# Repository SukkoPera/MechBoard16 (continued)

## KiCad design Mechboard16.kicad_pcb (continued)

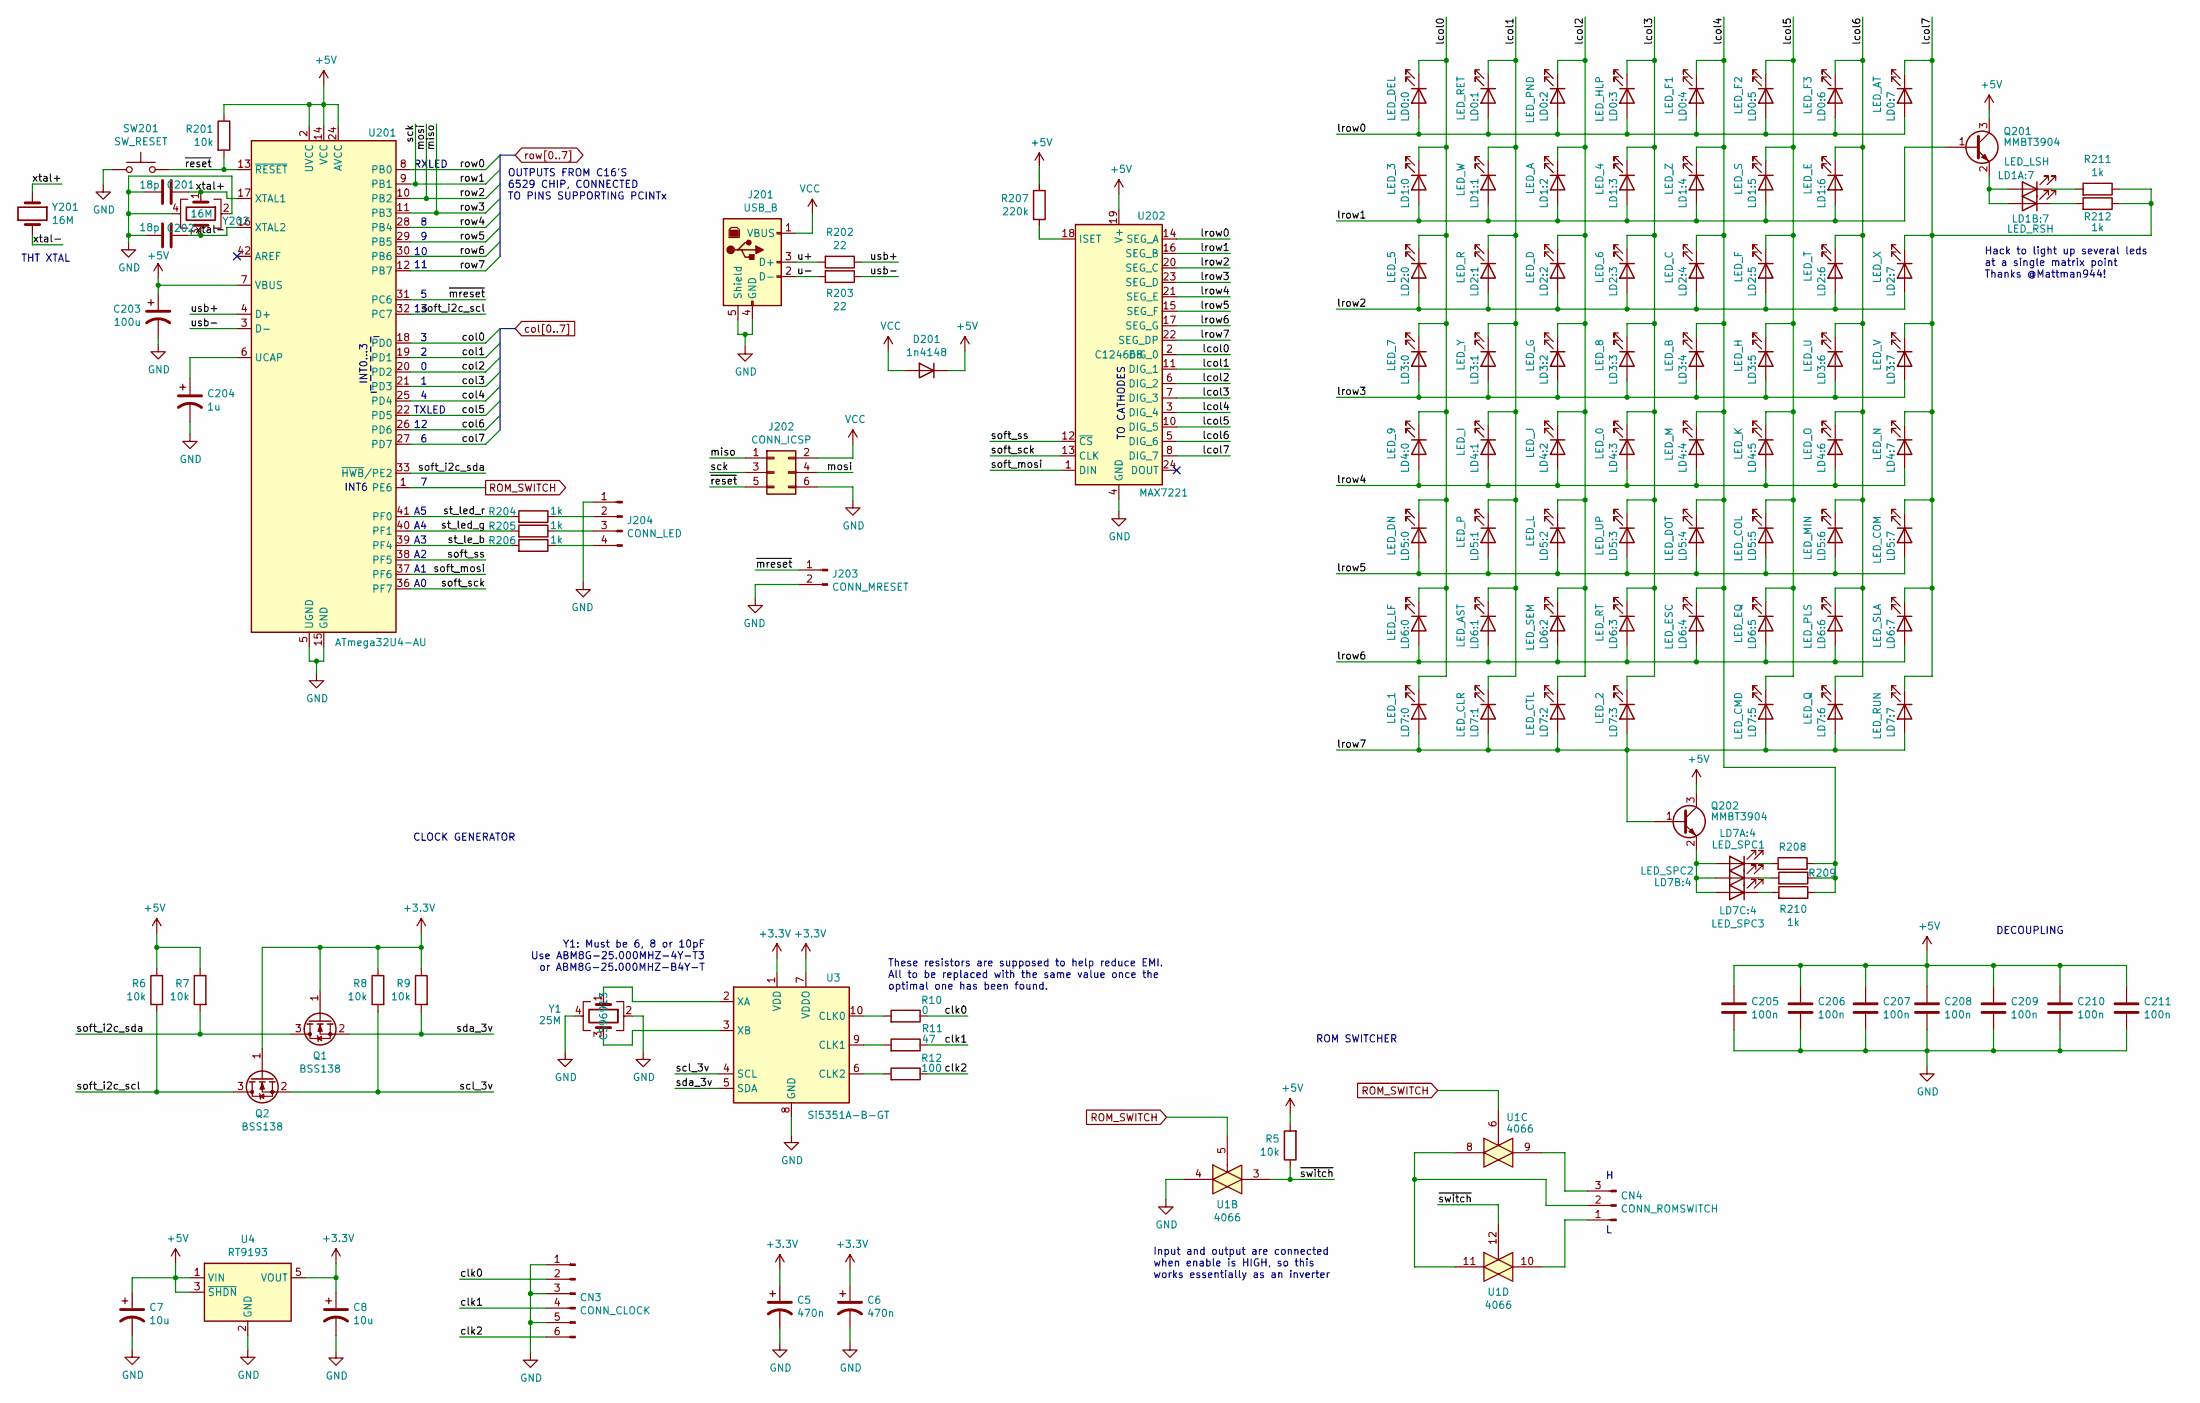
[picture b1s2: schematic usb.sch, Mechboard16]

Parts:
C5, C6: 470n; C_0805_2012Metric_Pad1.18x1.45mm_HandSolder; LCSC C13967
C7, C8: 10u; CP_Radial_D5.0mm_P2.00mm
C201, C202: 18p; C_0805_2012Metric_Pad1.18x1.45mm_HandSolder; LCSC C1804
C203: 100u; CP_Radial_D6.3mm_P2.50mm
C204: 1u; C_1206_3216Metric_Pad1.33x1.80mm_HandSolder; LCSC C1848
C205, C206, C207, C208, C209, C210, C211: 100n; C_0805_2012Metric_Pad1.18x1.45mm_HandSolder; LCSC C49678
CN3: CONN_CLOCK; PinHeader_1x06_P2.54mm_Vertical
CN4: CONN_ROMSWITCH; PinHeader_1x03_P2.54mm_Vertical
D201: 1n4148; D_SOD-323_HandSoldering; LCSC C2128
J201: USB_B; USB_B_OST_USB-B1HSxx_Horizontal
J202: CONN_ICSP; PinHeader_2x03_P2.54mm_Vertical
J203: CONN_MRESET; PinHeader_1x02_P2.54mm_Vertical
J204: CONN_LED; PinHeader_1x04_P2.54mm_Vertical
LD0:0: LED_DEL; LED_MX_6028R; LCSC C3646964
LD0:1: LED_RET; LED_MX_6028R; LCSC C3646964
LD0:2: LED_PND; LED_MX_6028R; LCSC C3646964
LD0:3: LED_HLP; LED_MX_6028R; LCSC C3646964
LD0:4: LED_F1; LED_MX_6028R; LCSC C3646964
LD0:5: LED_F2; LED_MX_6028R; LCSC C3646964
LD0:6: LED_F3; LED_MX_6028R; LCSC C3646964
LD0:7: LED_AT; LED_MX_6028R; LCSC C3646964
LD1:0: LED_3; LED_MX_6028R; LCSC C3646964
LD1:1: LED_W; LED_MX_6028R; LCSC C3646964
LD1:2: LED_A; LED_MX_6028R; LCSC C3646964
LD1:3: LED_4; LED_MX_6028R; LCSC C3646964
LD1:4: LED_Z; LED_MX_6028R; LCSC C3646964
LD1:5: LED_S; LED_MX_6028R; LCSC C3646964
LD1:6: LED_E; LED_MX_6028R; LCSC C3646964
LD1A:7: LED_LSH; LED_MX_6028R; LCSC C3646964
LD1B:7: LED_RSH; LED_MX_6028R; LCSC C3646964
LD2:0: LED_5; LED_MX_6028R; LCSC C3646964
LD2:1: LED_R; LED_MX_6028R; LCSC C3646964
LD2:2: LED_D; LED_MX_6028R; LCSC C3646964
LD2:3: LED_6; LED_MX_6028R; LCSC C3646964
LD2:4: LED_C; LED_MX_6028R; LCSC C3646964
LD2:5: LED_F; LED_MX_6028R; LCSC C3646964
LD2:6: LED_T; LED_MX_6028R; LCSC C3646964
LD2:7: LED_X; LED_MX_6028R; LCSC C3646964
LD3:0: LED_7; LED_MX_6028R; LCSC C3646964
LD3:1: LED_Y; LED_MX_6028R; LCSC C3646964
LD3:2: LED_G; LED_MX_6028R; LCSC C3646964
LD3:3: LED_8; LED_MX_6028R; LCSC C3646964
LD3:4: LED_B; LED_MX_6028R; LCSC C3646964
LD3:5: LED_H; LED_MX_6028R; LCSC C3646964
LD3:6: LED_U; LED_MX_6028R; LCSC C3646964
LD3:7: LED_V; LED_MX_6028R; LCSC C3646964
LD4:0: LED_9; LED_MX_6028R; LCSC C3646964
LD4:1: LED_I; LED_MX_6028R; LCSC C3646964
LD4:2: LED_J; LED_MX_6028R; LCSC C3646964
LD4:3: LED_0; LED_MX_6028R; LCSC C3646964
LD4:4: LED_M; LED_MX_6028R; LCSC C3646964
LD4:5: LED_K; LED_MX_6028R; LCSC C3646964
LD4:6: LED_O; LED_MX_6028R; LCSC C3646964
LD4:7: LED_N; LED_MX_6028R; LCSC C3646964
LD5:0: LED_DN; LED_MX_6028R; LCSC C3646964
LD5:1: LED_P; LED_MX_6028R; LCSC C3646964
LD5:2: LED_L; LED_MX_6028R; LCSC C3646964
LD5:3: LED_UP; LED_MX_6028R; LCSC C3646964
LD5:4: LED_DOT; LED_MX_6028R; LCSC C3646964
LD5:5: LED_COL; LED_MX_6028R; LCSC C3646964
LD5:6: LED_MIN; LED_MX_6028R; LCSC C3646964
LD5:7: LED_COM; LED_MX_6028R; LCSC C3646964
LD6:0: LED_LF; LED_MX_6028R; LCSC C3646964
LD6:1: LED_AST; LED_MX_6028R; LCSC C3646964
LD6:2: LED_SEM; LED_MX_6028R; LCSC C3646964
LD6:3: LED_RT; LED_MX_6028R; LCSC C3646964
LD6:4: LED_ESC; LED_MX_6028R; LCSC C3646964
LD6:5: LED_EQ; LED_MX_6028R; LCSC C3646964
LD6:6: LED_PLS; LED_MX_6028R; LCSC C3646964
LD6:7: LED_SLA; LED_MX_6028R; LCSC C3646964
LD7:0: LED_1; LED_MX_6028R; LCSC C3646964
LD7:1: LED_CLR; LED_MX_6028R; LCSC C3646964
LD7:2: LED_CTL; LED_MX_6028R; LCSC C3646964
LD7:3: LED_2; LED_MX_6028R; LCSC C3646964
LD7:5: LED_CMD; LED_MX_6028R; LCSC C3646964
LD7:6: LED_Q; LED_MX_6028R; LCSC C3646964
LD7:7: LED_RUN; LED_MX_6028R; LCSC C3646964
LD7A:4: LED_SPC1; LED_MX_6028R; LCSC C3646964
LD7B:4: LED_SPC2; LED_MX_6028R; LCSC C3646964
LD7C:4: LED_SPC3; LED_MX_6028R; LCSC C3646964
Q1, Q2: BSS138; SOT-23; LCSC C75547
Q201, Q202: MMBT3904; SOT-23; LCSC C20526
R5, R6, R7, R8, R9, R201: 10k; R_0805_2012Metric_Pad1.20x1.40mm_HandSolder; LCSC C17414
R10: 0; R_0805_2012Metric_Pad1.20x1.40mm_HandSolder; LCSC C17477
R11: 47; R_0805_2012Metric_Pad1.20x1.40mm_HandSolder; LCSC C17714
R12: 100; R_0805_2012Metric_Pad1.20x1.40mm_HandSolder; LCSC C17408
R202, R203: 22; R_0805_2012Metric_Pad1.20x1.40mm_HandSolder; LCSC C17561
R204, R205, R206, R208, R209, R210, R211, R212: 1k; R_0805_2012Metric_Pad1.20x1.40mm_HandSolder; LCSC C17513
R207: 220k; R_0805_2012Metric_Pad1.20x1.40mm_HandSolder; LCSC C17556
SW201: SW_RESET; SW_SPST_EVPBF; LCSC C318884
U1: 4066; SOIC-14_3.9x8.7mm_P1.27mm; LCSC C233577
U3: Si5351A-B-GT; MSOP-10_3x3mm_P0.5mm; MouserPN Si5351A-B02075-GT
U4: RT9193; SOT-23-5; LCSC C15651
U201: ATmega32U4-AU; TQFP-44_10x10mm_P0.8mm; LCSC C44854
U202: MAX7221; SOIC-24W_7.5x15.4mm_P1.27mm; LCSC C124668
Y1: 25M; Crystal_SMD_3225-4Pin_3.2x2.5mm; LCSC C596913
Y201: 16M; Crystal_HC49-4H_Vertical
Y202: 16M; Crystal_SMD_3225-4Pin_3.2x2.5mm; LCSC C13738

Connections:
+3V3: C5.1, C6.1, C8.1, Q1.1 (G), Q2.1 (G), R8.1, R9.1, U3.1 (VDD), U3.7 (VDDO), U4.5 (VOUT)
+5V: C7.1, C203.1, C205.1, C206.1, C207.1, C208.1, C209.1, C210.1, C211.1, D201.1 (K), Q201.3 (C), Q202.3 (C), R5.2, R6.1, R7.1, R201.1, R207.1, U4.1 (VIN), U4.3 (~SHDN), U201.2 (UVCC), U201.7 (VBUS), U201.14 (VCC), U201.24 (AVCC), U201.34 (VCC), U201.44 (AVCC), U202.19 (V+); also elsewhere on the board
/USB Controller/clk0: CN3.2, R10.1
/USB Controller/clk1: CN3.4, R11.1
/USB Controller/clk2: CN3.6, R12.1
/USB Controller/lcol0: LD0:0.1 (K), LD1:0.1 (K), LD2:0.1 (K), LD3:0.1 (K), LD4:0.1 (K), LD5:0.1 (K), LD6:0.1 (K), LD7:0.1 (K), U202.2 (DIG_0)
/USB Controller/lcol1: LD0:1.1 (K), LD1:1.1 (K), LD2:1.1 (K), LD3:1.1 (K), LD4:1.1 (K), LD5:1.1 (K), LD6:1.1 (K), LD7:1.1 (K), U202.11 (DIG_1)
/USB Controller/lcol2: LD0:2.1 (K), LD1:2.1 (K), LD2:2.1 (K), LD3:2.1 (K), LD4:2.1 (K), LD5:2.1 (K), LD6:2.1 (K), LD7:2.1 (K), U202.6 (DIG_2)
/USB Controller/lcol3: LD0:3.1 (K), LD1:3.1 (K), LD2:3.1 (K), LD3:3.1 (K), LD4:3.1 (K), LD5:3.1 (K), LD6:3.1 (K), LD7:3.1 (K), U202.7 (DIG_3)
/USB Controller/lcol4: LD0:4.1 (K), LD1:4.1 (K), LD2:4.1 (K), LD3:4.1 (K), LD4:4.1 (K), LD5:4.1 (K), LD6:4.1 (K), R208.1, R209.1, R210.1, U202.3 (DIG_4)
/USB Controller/lcol5: LD0:5.1 (K), LD1:5.1 (K), LD2:5.1 (K), LD3:5.1 (K), LD4:5.1 (K), LD5:5.1 (K), LD6:5.1 (K), LD7:5.1 (K), U202.10 (DIG_5)
/USB Controller/lcol6: LD0:6.1 (K), LD1:6.1 (K), LD2:6.1 (K), LD3:6.1 (K), LD4:6.1 (K), LD5:6.1 (K), LD6:6.1 (K), LD7:6.1 (K), U202.5 (DIG_6)
/USB Controller/lcol7: LD0:7.1 (K), LD2:7.1 (K), LD3:7.1 (K), LD4:7.1 (K), LD5:7.1 (K), LD6:7.1 (K), LD7:7.1 (K), R211.1, R212.1, U202.8 (DIG_7)
/USB Controller/lrow0: LD0:0.2 (A), LD0:1.2 (A), LD0:2.2 (A), LD0:3.2 (A), LD0:4.2 (A), LD0:5.2 (A), LD0:6.2 (A), LD0:7.2 (A), U202.14 (SEG_A)
/USB Controller/lrow1: LD1:0.2 (A), LD1:1.2 (A), LD1:2.2 (A), LD1:3.2 (A), LD1:4.2 (A), LD1:5.2 (A), LD1:6.2 (A), Q201.1 (B), U202.16 (SEG_B)
/USB Controller/lrow2: LD2:0.2 (A), LD2:1.2 (A), LD2:2.2 (A), LD2:3.2 (A), LD2:4.2 (A), LD2:5.2 (A), LD2:6.2 (A), LD2:7.2 (A), U202.20 (SEG_C)
/USB Controller/lrow3: LD3:0.2 (A), LD3:1.2 (A), LD3:2.2 (A), LD3:3.2 (A), LD3:4.2 (A), LD3:5.2 (A), LD3:6.2 (A), LD3:7.2 (A), U202.23 (SEG_D)
/USB Controller/lrow4: LD4:0.2 (A), LD4:1.2 (A), LD4:2.2 (A), LD4:3.2 (A), LD4:4.2 (A), LD4:5.2 (A), LD4:6.2 (A), LD4:7.2 (A), U202.21 (SEG_E)
/USB Controller/lrow5: LD5:0.2 (A), LD5:1.2 (A), LD5:2.2 (A), LD5:3.2 (A), LD5:4.2 (A), LD5:5.2 (A), LD5:6.2 (A), LD5:7.2 (A), U202.15 (SEG_F)
/USB Controller/lrow6: LD6:0.2 (A), LD6:1.2 (A), LD6:2.2 (A), LD6:3.2 (A), LD6:4.2 (A), LD6:5.2 (A), LD6:6.2 (A), LD6:7.2 (A), U202.17 (SEG_G)
/USB Controller/lrow7: LD7:0.2 (A), LD7:1.2 (A), LD7:2.2 (A), LD7:3.2 (A), LD7:5.2 (A), LD7:6.2 (A), LD7:7.2 (A), Q202.1 (B), U202.22 (SEG_DP)
/USB Controller/scl_3v: Q2.2 (S), R8.2, U3.4 (SCL)
/USB Controller/sda_3v: Q1.2 (S), R9.2, U3.5 (SDA)
/USB Controller/soft_i2c_scl: Q2.3 (D), R6.2, U201.32 (PC7)
/USB Controller/soft_i2c_sda: Q1.3 (D), R7.2, U201.33 (~HWB~/PE2)
/USB Controller/soft_mosi: U201.37 (PF6), U202.1 (DIN)
/USB Controller/soft_sck: U201.36 (PF7), U202.13 (CLK)
/USB Controller/soft_ss: U201.38 (PF5), U202.12 (~CS)
/USB Controller/st_le_b: R206.2, U201.39 (PF4)
/USB Controller/st_led_g: R205.2, U201.40 (PF1)
/USB Controller/st_led_r: R204.2, U201.41 (PF0)
/USB Controller/u+: J201.3 (D+), R202.2
/USB Controller/u-: J201.2 (D-), R203.2
/USB Controller/usb+: R202.1, U201.4 (D+)
/USB Controller/usb-: R203.1, U201.3 (D-)
/USB Controller/xtal+: C201.1, U201.17 (XTAL1), Y201.1, Y202.1
/USB Controller/xtal-: C202.1, U201.16 (XTAL2), Y201.2, Y202.3
/USB Controller/~mreset: J203.1, U201.31 (PC6)
/USB Controller/~reset: J202.5, R201.2, SW201.2, U201.13 (~RESET)
/USB Controller/~switch: R5.1, U1.3, U1.12
GND: C5.2, C6.2, C7.2, C8.2, C201.2, C202.2, C203.2, C204.2, C205.2, C206.2, C207.2, C208.2, C209.2, C210.2, C211.2, CN3.1, CN3.3, CN3.5, J201.4 (GND), J201.5 (Shield), J202.6, J203.2, J204.1, SW201.1, U1.4, U3.8 (GND), U4.2 (GND), U201.5 (UGND), U201.15 (GND), U201.23 (GND), U201.35 (GND), U201.43 (GND), U202.4 (GND), U202.9 (GND), Y1.2, Y1.4, Y202.2, Y202.4; also elsewhere on the board
unnamed: C204.1, U201.6 (UCAP)
unnamed: CN4.1, U1.10
unnamed: CN4.2, U1.8, U1.11
unnamed: CN4.3, U1.9
unnamed: J204.2, R204.1
unnamed: J204.3, R205.1
unnamed: J204.4, R206.1
unnamed: LD1A:7.1 (K), R211.2
unnamed: LD1A:7.2 (A), LD1B:7.2 (A), Q201.2 (E)
unnamed: LD1B:7.1 (K), R212.2
unnamed: LD7A:4.1 (K), R208.2
unnamed: LD7A:4.2 (A), LD7B:4.2 (A), LD7C:4.2 (A), Q202.2 (E)
unnamed: LD7B:4.1 (K), R209.2
unnamed: LD7C:4.1 (K), R210.2
unnamed: R10.2, U3.10 (CLK0)
unnamed: R11.2, U3.9 (CLK1)
unnamed: R12.2, U3.6 (CLK2)
unnamed: R207.2, U202.18 (ISET)
unnamed: U3.2 (XA), Y1.1
unnamed: U3.3 (XB), Y1.3
ROM_SWITCH: U1.5, U1.6, U201.1 (PE6)
VCC: D201.2 (A), J201.1 (VBUS), J202.2
col0: U201.18 (PD0); also elsewhere on the board
col1: U201.19 (PD1); also elsewhere on the board
col2: U201.20 (PD2); also elsewhere on the board
col3: U201.21 (PD3); also elsewhere on the board
col4: U201.25 (PD4); also elsewhere on the board
col5: U201.22 (PD5); also elsewhere on the board
col6: U201.26 (PD6); also elsewhere on the board
col7: U201.27 (PD7); also elsewhere on the board
row0: U201.8 (PB0); also elsewhere on the board
row1: J202.3, U201.9 (PB1); also elsewhere on the board
row2: J202.4, U201.10 (PB2); also elsewhere on the board
row3: J202.1, U201.11 (PB3); also elsewhere on the board
row4: U201.28 (PB4); also elsewhere on the board
row5: U201.29 (PB5); also elsewhere on the board
row6: U201.30 (PB6); also elsewhere on the board
row7: U201.12 (PB7); also elsewhere on the board

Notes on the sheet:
DECOUPLING
TXLED
INT0...3
INT6
RXLED
OUTPUTS FROM C16'S 6529 CHIP, CONNECTED TO PINS SUPPORTING PCINTx
TO CATHODES
THT XTAL
Hack to light up several leds at a single matrix point Thanks @Mattman944!
Y1: Must be 6, 8 or 10pF Use ABM8G-25.000MHZ-4Y-T3 or ABM8G-25.000MHZ-B4Y-T
CLOCK GENERATOR
Input and output are connected when enable is HIGH, so this works essentially as an inverter
ROM SWITCHER
These resistors are supposed to help reduce EMI. All to be replaced with the same value once the optimal one has been found.

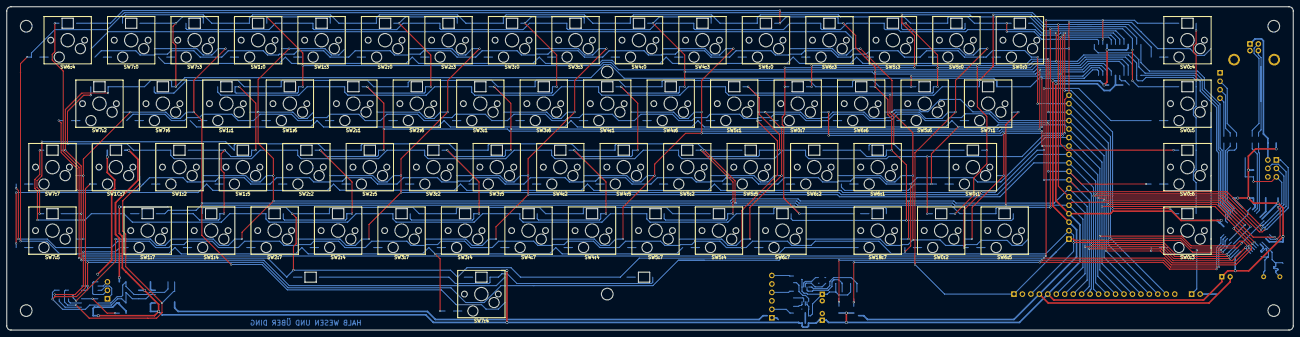
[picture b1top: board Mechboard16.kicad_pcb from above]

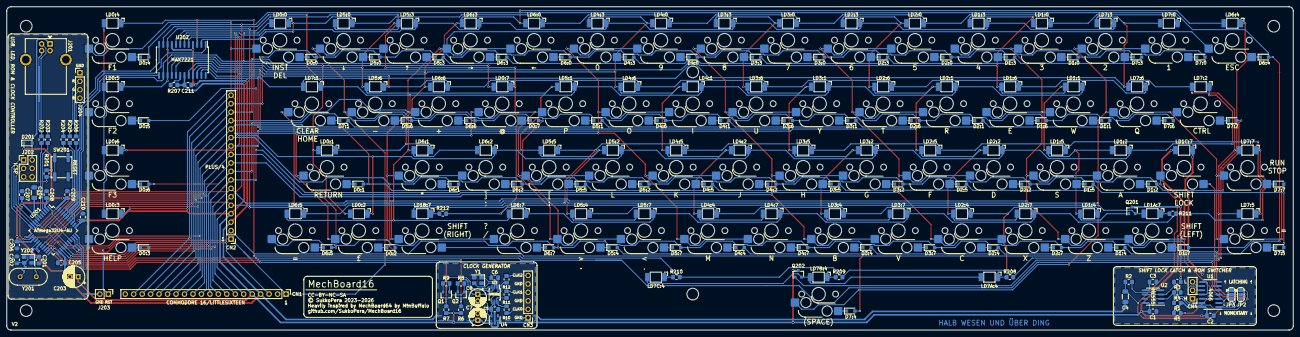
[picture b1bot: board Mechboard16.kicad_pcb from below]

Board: 2 copper layers, 386.1 x 97.0 mm, 274 parts (200 on the bottom side), 150 nets.

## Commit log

2023-10-12 Work in progress
2023-10-13 Schematics should be final
2023-10-13 Routing in progress
2023-10-14 Add screw holes
2023-10-14 Routing done
2023-10-14 Change JP2 to solder jumper(s)
2023-10-14 Add key markings on back
2023-10-14 Add README
2023-10-15 Add RP2040 board so that keybord can be used as a HID device
2023-10-15 Hone silkscreen
2023-10-15 Add RP2040 reference
2023-10-15 Widen ground plane for Shift Lock circuit
2023-10-15 Add LCSC P/Ns
2023-10-15 Fix position of Return key
2023-10-18 Better alignment of R3 and start adding centered footprints for 1.5U keys
2023-11-25 Add ATmega32U4, MAX7221 and leeeeeds! Routing TBD ^___^
2023-11-25 LED routing in progress...
2023-11-26 WIP2
2023-11-26 I'm tired and I want to go to bed
2023-11-27 I need to drink more than you seem to think
2023-11-27 HEEEEEAAAADLOOOOOOOOOOONGGG!
2023-11-27 Almost there...
2023-11-28 Done! Just some finishing touches left...
2023-11-28 Add legend on J204
2023-11-28 Move SMD resistors
2023-11-28 Happy?
2023-11-28 Finaaaaaaaaaal touches
2023-11-29 IN PRODUCTION!
2023-11-29 Make 1u caps uniform
2023-12-10 R4 ready for hybrid MX/Matias switches and fix some inconsitencies in routing
2023-12-16 R3 done
2023-12-16 R2 done
2023-12-16 R1 done
2023-12-16 Switch non-1.00u keys to hybrid
2023-12-16 Better stabilizer holes
2023-12-17 Back to MX-only and minor routing adjustments
2023-12-17 Add screw holes on Eco1
2024-01-08 Add extra Spacebar led holes on Eco1
2024-01-11 Flip all diodes, sigh...
2025-10-26 Add drawing & pic of power mod
2025-10-26 Fix photo link
2025-10-26 Add all double footprints
2025-10-26 Add license
2025-10-26 Update board link
2025-10-26 Remove output directory
2025-10-26 Update license info
2025-10-26 Add badges
2025-12-21 Most horizontal key and led connections done
2025-12-21 Begin adding Kailh MX sockets
2025-12-21 Row 3 done
2025-12-21 Switch to MX sockets
2025-12-21 Turning sockets upside-down and switching to SMD leds
2025-12-21 Routing... Routing... Routing...
2025-12-22 Rough routing complete, but still lots to do
2025-12-22 Add clock generator circuit
2025-12-22 Fix all DRC
2025-12-22 Remove power jumper
2025-12-22 Make LED hole more square
2025-12-22 Much refining
2025-12-23 Some THT components -> SMD
2025-12-23 Preparing for PCBA
2025-12-23 Slight reword in clock generator area
2025-12-23 Add ROM switcher
2025-12-24 Add series resistors on clock outputs
2025-12-24 Almost there
2026-01-13 Ready for V2 RC1
